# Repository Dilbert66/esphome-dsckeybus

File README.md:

# DSCKeyBus ESPHOME custom component to interface to a DSC POWERSERIES alarm system.

If you like this project and wish to supplement my coffee intake, please click the button below to donate! Thank you!

This is an implementation of an ESPHOME custom component to interface directly to a [DSC POWERSERIES] (https://www.dsc.com/dsc-security-products/g/PowerSeries/4)  alarm system using the keybus interface and  very inexpensive ESP32 modules.  Dsc Classic series is not currently supported.  

*** NOTE *** : The ESP8266 is no longer supported due to it having inadequate resources needed to run the current code base since ESPHome version 2025.7  

Using a heavily modified DSC keybus interface library from https://github.com/taligentx/dscKeybusInterface, it provides full read and write control of the alarm system. The idea and yaml code is based on the DIY example at: https://github.com/Margriko/Paradox-ESPHome.

This library is designed around the "external components" feature of ESPHome (https://esphome.io/components/external_components.html).  The previous version of this library was using the older "custom components" feature which is being deprecated.  Using external components is a much better alternative and allows for much easier install and customization.

To install, first copy the DscAlarm.yaml file from here to your esphome directory. You can then edit it either directly or using the ESPHome dashboard to match your alarm panel setup.  The yaml is self explanatory.  Secondly, for the main library support code installation you have two choices:

 1: You can leave the yaml external_components source line uncommented and it will automatically fetch the required code from my esphome-components repository during the compile.  
 
 or alternatively:
 
 2: If you prefer a more manual approach, you can comment out the github source line and uncomment the source "my_components" line.  You will then need to create a matching my_components directory in your esphome home path.  Name it anything you like as long as it matches the source line in the yaml.  You then copy all content from the "components" directory located in repository https://github.com/Dilbert66/esphome-components/tree/main/ to this new directory. Please note that for any future updates, you will again need to do the copy process.

The following services are published to home assistant for use in various scripts.  Please note that you will also need to have a transistor on the green data line to give you write access to the bus as shown in the wiring diagram.

	alarm_disarm: Disarms the alarm with the user code provided, or the code specified in the configuration.
	alarm_arm_home: Arms the alarm in home mode.
	alarm_arm_away: Arms the alarm in away mode.
	alarm_arm_night: Arms the alarm in night mode (no entry delay).
	alarm_trigger_panic: Trigger a panic alarm.
        alarm_trigger_fire: Trigger a fire alarm.
	alarm_keypress_partition: Sends a string of characters to the alarm system to the selected partition
        set_zone_fault: Triggers a open/close on one of the zone emulator virtual zones
	set_panel_time: Set the time on your panel. For the esp32 on. Automatically syncs the time with an nntp server.
	set_panel_time_manual: Set the time on your panel directly.

These are similar services to those provided by the Envisalink Home Assistant integration (which requires a more expensive Envisalink interface board to be installed in your alarm system panel). See: https://www.home-assistant.io/integrations/envisalink/

A new feature of the firmware is the ability to emulate multiple PC5108 zone adapaters to give you up to 64 zones if your system supports it. Example configuration to add emulation of zones 17-24 in the dscalarm.yaml file.  

Example config: 
```
  #zone expander addresses:
  # 9  - zones 9-16
  # 10 - zones 17-24
  # 11 - zones 25-32
  # 12 - zones 33-40 (for systems with 64 zone support)
  # 13 - zones 41-48 (for systems with 64 zone support)
  # 14 - zones 49-56 (for systems with 64 zone support)
  # 16 - zones 57-64 (for systems with 64 zone support)  
  expanderAddr1: "10" # 1st zone expander emulator address to use . Set to 0 to disable. 
  expanderAddr2: "0" # 2nd expander emulator address to use . Set to 0 to disable. 
```
A new service is also made available in home assistant called  esphome.\<yourdscsystemname\>_set_zone_fault with attributes zone and fault: 
zone is 2 digit zone number and fault is 0 or 1 where 1 sets a zone as open and 0 closes it. By calling this service from a home assistant function, you can enable any event, sensor, etc to trigger any one of your emulated zones in your alarm system.

Relay module support is also added.   This will give your panel the ability to trigger an event on any PGM channel output.  See the yaml file for an example configuration.  An example output for pgm 1 will show in home assistant as <systemname> PGM 1. You can add more fields in the yaml config file.

This version now also adds the ability to display the low battery warning status of any wireless zones.  These will be showng in the "zone status" field of the yaml.   Also in that field, you will see the alarm status, open and bypass statuses of any zones
The display format for a low battery is BL:zz and alarm status will be shown as AL:zz  where zz is the zone number.  Bypass is BY:xx and open is OP:xx.

I've also added a custom alarm panel card with new  functions from the library that provides similar functions as available from an LCD keypad.  This includes the display menus and the ability to fully program your system using full text display of all fields.
	
## Example in Home Assistant

The returned statuses for Home Assistant are: armed_away, armed_home, armed_night, pending, disarmed,triggered and unavailable.  

Sample Home Assistant Template Alarm Control Panel configuration with simple services (defaults to partition 1).

```
alarm_control_panel:
  - platform: template
    panels:
      safe_alarm_panel:
        name: "Alarm Panel"
        value_template: "{{states('sensor.dscalarm_status_partition_1')}}"
        code_arm_required: false
        
        arm_away:
           action: esphome.dscalarm_alarm_arm_away
                  
        arm_home:
           action: esphome.dscalarm_alarm_arm_home
          
        arm_night:
           action: esphome.dscalarm_alarm_arm_night
            data_template:
              code: '{{code}}' #if you didnt set it in the yaml, then send the code here
          
        disarm:
           action: esphome.dscalarm_alarm_disarm
            data_template:
              code: '{{code}}'                    

```

Alternative Home assistant configuration using specified partition with set_alarm_state service.

```
alarm_control_panel:
  - platform: template
    panels:
      safe_alarm_panel:
        name: "Alarm Panel - Partition 2"
        value_template: "{{states('sensor.dscalarm_status_partition_1')}}"
        code_arm_required: false
        
        arm_away:
           action: esphome.dscalarm_set_alarm_state
            data_template:
			  partition: 2
			  state: "A"
			  code: ""
      
        arm_home:
           action: esphome.dscalarm_set_alarm_state
            data_template:
              partition: 2
			  state: "S"
			  code: ""

        arm_night:
           action: esphome.dscalarm_set_alarm_state
            data_template:
              partition: 2
              state: "N"
              code: '{{code}}'  
          
        disarm:
          - service: esphome.dscalarm_set_alarm_state
            data_template:
              partition: 2
              state: "D"
              code: '{{code}}'            
```
## Services

- Basic alarm services. These services default to partition 1:

	- "alarm_disarm", Parameter: "code" (access code)
	- "alarm_arm_home" 
	- "alarm_arm_night", Parameter: "code" (access code)
	- "alarm_arm_away"
	- "alarm_trigger_panic"
	- "alarm_trigger_fire"
    - "set_zone_fault", Parameters: "zone" , "fault" eg zone: 17, fault: 1 (or true) 

- Intermediate command service. Use this service if you need more versatility such as setting alarm states on any partition:

	- "set_alarm_state",  Parameters: "partition","state","code"  where partition is the partition number from 1 to 8, state is one of "D" (disarm), "A" (arm_away), "S" (arm_home), "N" (arm_night), "P" (panic) or "F" (fire) and "code" is your panel access code (can be empty for arming, panic and fire cmds )

- Generic command service. Use this service for more complex control:

	- "alarm_keypress",  Parameter: "keys" where keys can be any sequence of cmds from the list below. For example to arm partition 2  in night mode you set keys to be "/2Nxxxx" where xxxx is your access code. Alternatively you can use the * code for the same function and send /2*9xxxx.   

```
	  case '/': setPartition = true; validKey = false; break;
      case '0':
      case '1': writeKey = 0x05; break;
      case '2': writeKey = 0x0A; break;
      case '3': writeKey = 0x0F; break;
      case '4': writeKey = 0x11; break;
      case '5': writeKey = 0x16; break;
      case '6': writeKey = 0x1B; break;
      case '7': writeKey = 0x1C; break;
      case '8': writeKey = 0x22; break;
      case '9': writeKey = 0x27; break;
      case '*': writeKey = 0x28; writeAsterisk = true; break;
      case '#': writeKey = 0x2D; break;
      case 'F':
      case 'f': writeKey = 0x77; writeAlarm = true; break;                    // Keypad fire alarm
      case 's':
      case 'S': writeKey = 0xAF; writeArm[writePartition - 1] = true; break;  // Arm stay
      case 'w':
      case 'W': writeKey = 0xB1; writeArm[writePartition - 1] = true; break;  // Arm away
      case 'n':
      case 'N': writeKey = 0xB6; writeArm[writePartition - 1] = true; break;  // Arm with no entry delay (night arm)
      case 'A':
      case 'a': writeKey = 0xBB; writeAlarm = true; break;                    // Keypad auxiliary alarm
      case 'c':
      case 'C': writeKey = 0xBB; break;                                       // Door chime
      case 'r':
      case 'R': writeKey = 0xDA; break;                                       // Reset
      case 'P':
      case 'p': writeKey = 0xDD; writeAlarm = true; break;                    // Keypad panic alarm
      case 'x':
      case 'X': writeKey = 0xE1; break;                                       // Exit
      case '[': writeKey = 0xD5; break;                                       // Command output 1
      case ']': writeKey = 0xDA; break;                                       // Command output 2
      case '{': writeKey = 0x70; break;                                       // Command output 3
      case '}': writeKey = 0xEC; break;                                       // Command output 4
```	 

## Custom Alarm Panel Card
I've added a sample lovelace alarm-panel card copied from the repository at https://github.com/GalaxyGateway/HA-Cards. I've customized it to work with this ESP library's services.   I've also added two new text fields that will be used by the card to display the panel prompts the same way a real keypad does. To configure the card, just place the `alarm-keypad-card.js` and `*.mp3` files from the ha_keypad_card folder into the `/config/www` directory of your homeassistant installation and add a new resource in your lovelace configuration pointing to `/local/alarm-keypad-card.js`. <br>
Add a reference to alarm-keypad-card.js in Lovelace. There’s two ways to do that:<br>
1. Using UI:  go to settings (cog icon bottom left in sidebar menu), click on 'dashboards', click on top right 3 dots option then on Resources,
  bottom right 'add resource' option, in window, paste the url as '/local/alarm-keypad-card.js?id=1', select javascript module.

2. Using YAML: Add following code to lovelace section

```yaml
resources:
- url: /local/alarm-keypad-card.js?id=1
  type: module
```
*** NOTE *** :  Every time you update this file, you will need to increase the id=xx number in the url by 1 in order to force the browser to reload it.

### Panel Card example

### Panel card example lovelace configuration

```
type: custom:alarm-keypad-card
title: DSC Keypad
disp_line1: sensor.dscalarm_ln1_1
disp_line2: sensor.dscalarm_ln2_1
service_type: esphome
service: dscalarm_alarm_keypress_partition
status_A: READY
status_B: ARMED
status_C: TROUBLE
status_D: AC
sensor_A: binary_sensor.dscalarm_rdy_1
sensor_B: binary_sensor.dscalarm_arm_1
sensor_C: binary_sensor.dscalarm_tr
sensor_D: binary_sensor.dscalarm_ac
status_A_off_icon: mdi:circle-off-outline
status_A_on_icon: mdi:check-circle
status_A_color: green
status_B_on_icon: mdi:shield-lock
status_B_off_icon: mdi:shield-off-outline
status_B_color: red
status_C_on_icon: mdi:alert
status_C_off_icon: mdi:triangle-outline
status_C_color: orange
status_D_on_icon: mdi:power-plug
status_D_off_icon: mdi:power-plug-off-outline
status_D_color: green

#all style/color settings are optional. These are the default for dark and light modes
style:
  "--lcdbgcolordark": "#859c99"
  "--lcdtextcolordark": "#222"
  "--buttonbgcolordark": var(--input-fill-color)
  "--buttontextcolordark": var(--primary-color)
  "--buttonhovercolordark": var(--outline-hover-color)
  "--buttonactivecolordark": var(--secondary-text-color)
  "--sensorlabelcolordark": var(--accent-color));
  "--buttonfocuscolordark": var(--outline-color)
  "--sensoroffcolordark": var(--disabled-text-color)
  "--bordercolordark": var(--disabled-color)

  "--sensoroffcolorlight": var(--disabled-text-color)
  "--lcdbgcolorlight": "#859c99"
  "--lcdtextcolorlight": "#222"
  "--sensorlabelcolorlight": var(--accent-color));
  "--buttonbgcolorlight": var(--input-fill-color)
  "--buttontextcolorlight": var(--primary-color)
  "--buttonhovercolorlight": var(--outline-hover-color)
  "--buttonactivecolorlight": var(--secondary-text-color)
  "--buttonfocuscolorlight": var(--outline-color)
  "--bordercolorlight": var(--disabled-color)

button_A: STAY
button_B: AWAY
button_C: NIGHT
button_D: CHIME
button_E: ""
button_F: <
button_G: ">"
button_H: ""
cmd_A:
  keys: S
  partition: 1
cmd_B:
  keys: W
  partition: 1
cmd_C:
  keys: "N"
  partition: 1
cmd_D:
  keys: C
  partition: 1
cmd_F:
  keys: <
  partition: 1
cmd_G:
  keys: ">"
  partition: 1
key_0:
  keys: "0"
  partition: 1
key_1:
  keys: "1"
  partition: 1
key_2:
  keys: "2"
  partition: 1
key_3:
  keys: "3"
  partition: 1
key_4:
  keys: "4"
  partition: 1
key_5:
  keys: "5"
  partition: 1
key_6:
  keys: "6"
  partition: 1
key_7:
  keys: "7"
  partition: 1
key_8:
  keys: "8"
  partition: 1
key_9:
  keys: "9"
  partition: 1
key_star:
  keys: "*"
  partition: 1
key_pound:
  keys: "#"
  partition: 1
text_1: BYPASS
text_2: SERV
text_3: ALARMS
text_4: CHIME
text_5: CODES
text_6: FUNC
text_7: OUTP
text_8: PROG
text_9: NIGHT
text_star: SELECT
text_pound: ENTER
text_0: ""
beep: binary_sensor.dscalarm_bp_1
button_disabled_A: false
button_disabled_B: false
button_disabled_C: false
button_disabled_D: false
button_disabled_E: true
button_disabled_F: false
button_disabled_G: false
button_disabled_H: true
scale: 1
left_buttons: false
view_bottom: true

```	

## MQTT Support
If you would like to use MQTT communications with Homeassistant or alternatively use ESPHOME with other platforms that can support MQTT, you can modify the configuration to use the MQTT protocol instead of the native HA API integration.  This simply involves the addtion of an mqtt: configuration section in the yaml and to remove the api: section.   Please see the ESPHOME MQTT documentation more details: https://esphome.io/components/mqtt.html .  For an example on how to configure the alarm-panel-card to use MQTT services, please see the lovelace.yaml file.  

Command topic is "&lt;yoursystemnameinesphome&gt;/alarm/set"
	
Command payload for sending key commands: {"keys":"&lt;sequenceofkeys&gt;","partition":&lt;partition#&gt;}
	
Command payload to set an expander fault status: {"zone":&lt;zone#&gt;,"fault":&lt;on:off or 0:1&gt;}
	
Command payload to set an alarm state: {"state":"&lt;alarmstate&gt;","partition":&lt;partition#&gt;,"code":"&lt;accesscode&gt;"} - see set_alarm_state api command above for more details

Sensor data will follow the HA MQTT discovery format. See here for details: https://www.home-assistant.io/docs/mqtt/discovery/

If you prefer to use Arduino instead of ESPHome, I've also provided an Arduino example sketch in the mqtt_example folder.  Follow the instructions at the top of the file.
	
## Wiring
### Mosfet level converter version - recommended

Notes: You need to set dscreadpin = dscwritepin in the yaml config.  eg: dscwritepin: 21, dscreadpin: 21, dscclockpin: 22
This version uses a bidrectional read/write configuration for the green line. The yellow line is read only.
Thanks to utmba95 for the design suggestion and testing.

### Resistor divider version	

Notes: Write access to the Keybus requires an NPN transistor and a resistor.  Most small signal NPN transistors should be suitable.

## Optocoupler ground isolated version

* esp32: connect the DSC lines to GPIO pins that are normally low to avoid putting spurious data on the Keybus: GPIO22, GPIO21 and GPIO18.

* When powering the ESP from an external power supply such as USB (recommended) ensure you still connect the ground to the DSC panel if you are not using the isolated circuit version.

## Useful tools
jpmeijers has generously provided a python script to allow getting the installer code from a DSC panel.  See the README and associated files in the extras\crack_installer_code folder

## References
* ESPHOME yaml and component structure based on code from https://github.com/Margriko/Paradox-ESPHome
* Wiring and DSC library from https://github.com/taligentx/dscKeybusInterface
* ESPHOME diy examples from https://esphome.io/guides/diy.html
* Thanks to jpmeijers for the unlock script
* Also many thanks to the various people who have helped updating this library by testing and posting logs.

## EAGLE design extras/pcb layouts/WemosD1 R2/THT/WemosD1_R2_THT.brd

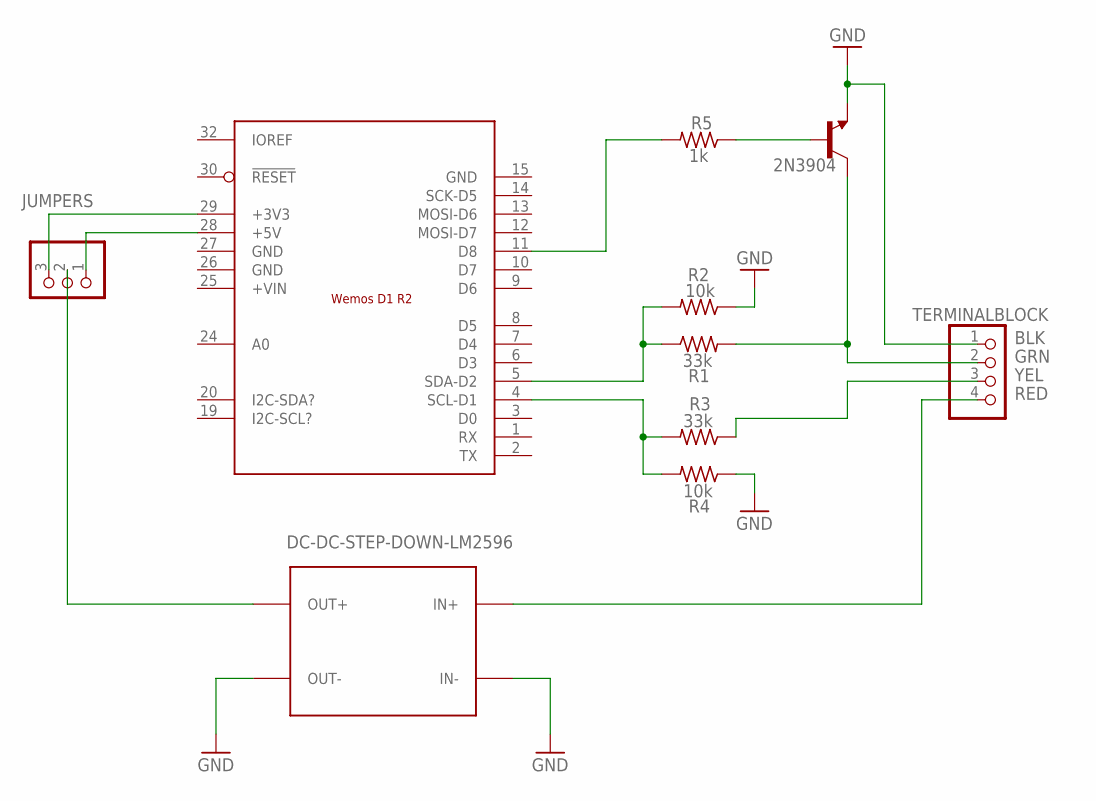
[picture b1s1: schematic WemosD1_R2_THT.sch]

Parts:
JUMPERS: PINHD-1X3; 1X03
R1, R3: 33k; 0204/7
R2, R4: 10k; 0204/7
R5: 1k; 0204/7
T1: 2N3904; TO92
TERMINALBLOCK: PINHD-1X4; 1X04
U$1: WEMOS_D1_R2
U$2: DC-DC-STEP-DOWN-LM2596

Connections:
GND: R2.1, R4.1, T1.3 (E), TERMINALBLOCK.1, U$1.15 (GND), U$1.26 (GND), U$1.27 (GND), U$2.IN-, U$2.OUT-
unnamed: R1.1, R2.2, U$1.5 (SDA-D2)
unnamed: JUMPERS.2, U$2.OUT+
unnamed: R3.2, R4.2, U$1.4 (SCL-D1)
unnamed: R3.1, TERMINALBLOCK.3
unnamed: TERMINALBLOCK.4, U$2.IN+
unnamed: R5.1, T1.2 (B)
unnamed: R5.2, U$1.11 (D8)
unnamed: JUMPERS.3, U$1.29 (+3V3)
unnamed: JUMPERS.1, U$1.28 (+5V)
unnamed: R1.2, T1.1 (C), TERMINALBLOCK.2

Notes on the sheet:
RED
YEL
GRN
BLK

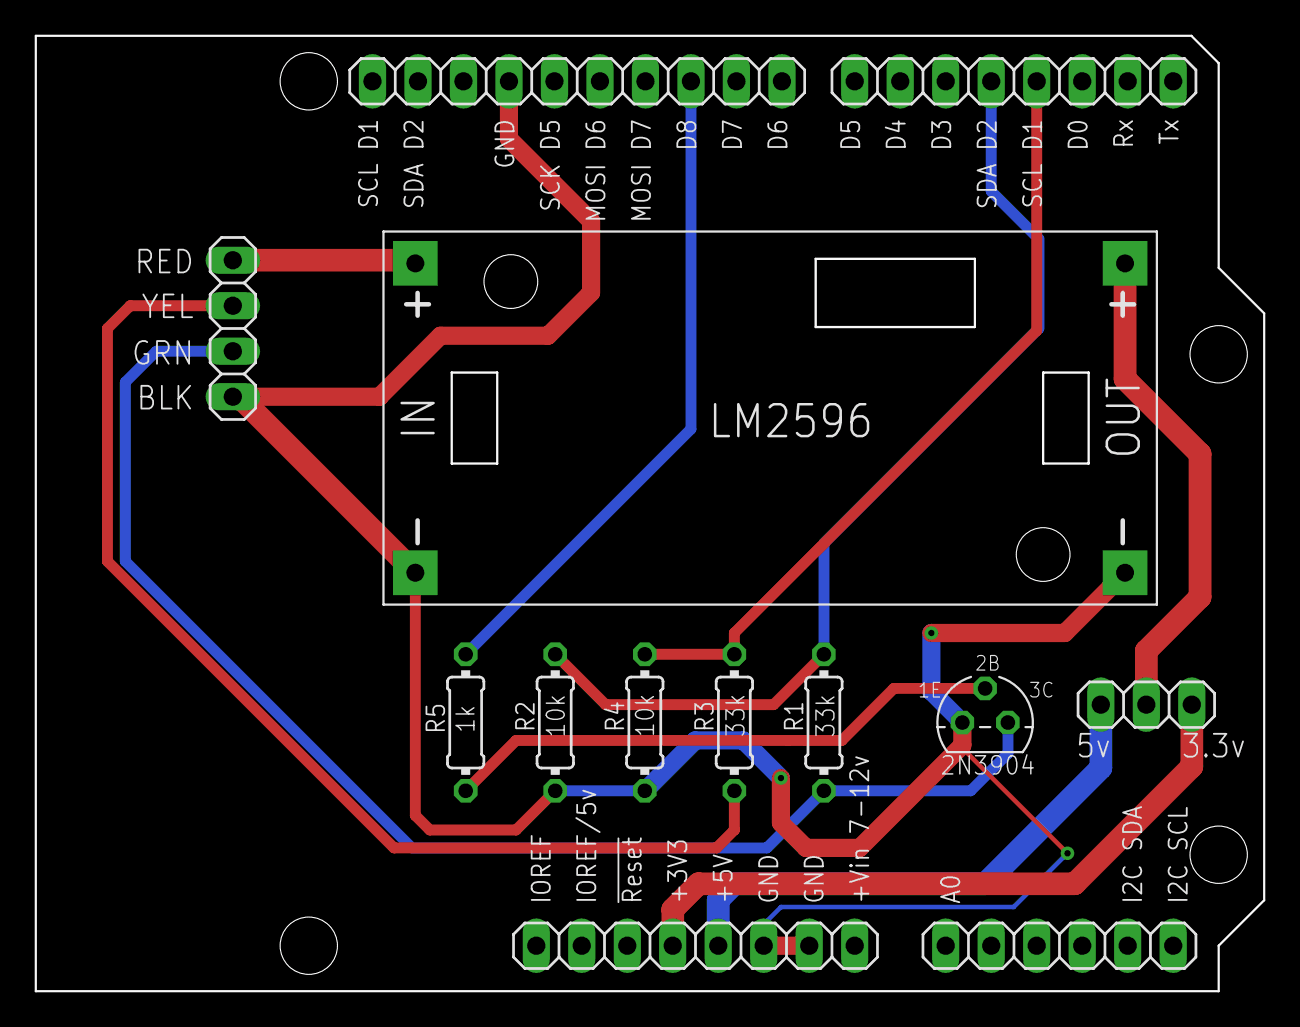
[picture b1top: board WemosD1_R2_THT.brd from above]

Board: 2 copper layers, 68.6 x 53.3 mm, 10 parts (0 on the bottom side), 11 nets.

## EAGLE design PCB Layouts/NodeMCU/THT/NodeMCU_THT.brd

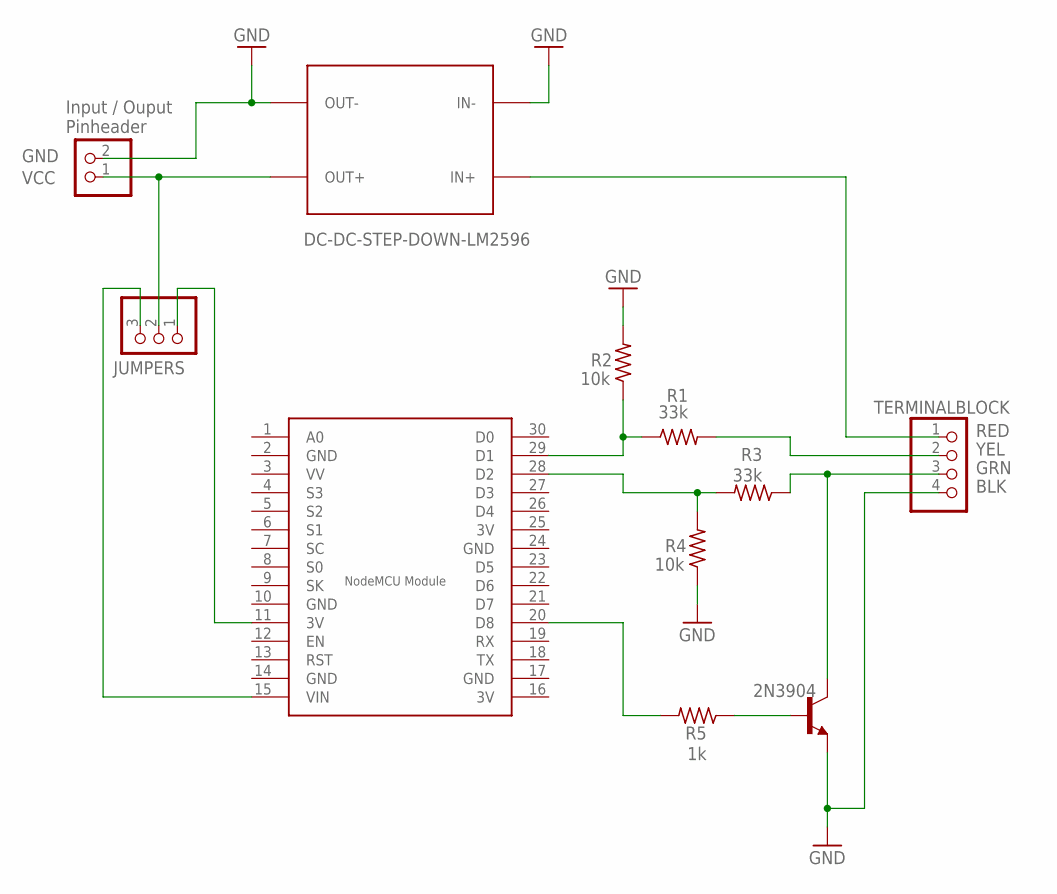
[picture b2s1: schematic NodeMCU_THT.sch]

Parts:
JP2: PINHD-1X2; 1X02
JUMPERS: PINHD-1X3; 1X03
R1, R3: 33k; 0204/7
R2, R4: 10k; 0204/7
R5: 1k; 0204/7
T1: 2N3904; TO92
TERMINALBLOCK: PINHD-1X4; 1X04
U$1: NODEMCU
U$2: DC-DC-STEP-DOWN-LM2596

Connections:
3V: U$1.16 (3V), U$1.25 (3V)
GND: JP2.2, R2.2, R4.1, T1.3 (E), TERMINALBLOCK.4, U$1.2 (GND), U$1.10 (GND), U$1.14 (GND), U$1.17 (GND), U$1.24 (GND), U$2.IN-, U$2.OUT-
unnamed: R1.1, R2.1, U$1.29 (D1)
unnamed: R1.2, TERMINALBLOCK.2
unnamed: R3.2, R4.2, U$1.28 (D2)
unnamed: R3.1, T1.1 (C), TERMINALBLOCK.3
unnamed: TERMINALBLOCK.1, U$2.IN+
unnamed: JP2.1, JUMPERS.2, U$2.OUT+
unnamed: R5.1, T1.2 (B)
unnamed: R5.2, U$1.20 (D8)
unnamed: JUMPERS.3, U$1.15 (VIN)
unnamed: JUMPERS.1, U$1.11 (3V)

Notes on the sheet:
NodeMCU Module
RED
YEL
GRN
BLK
GND
VCC
Input / Ouput Pinheader

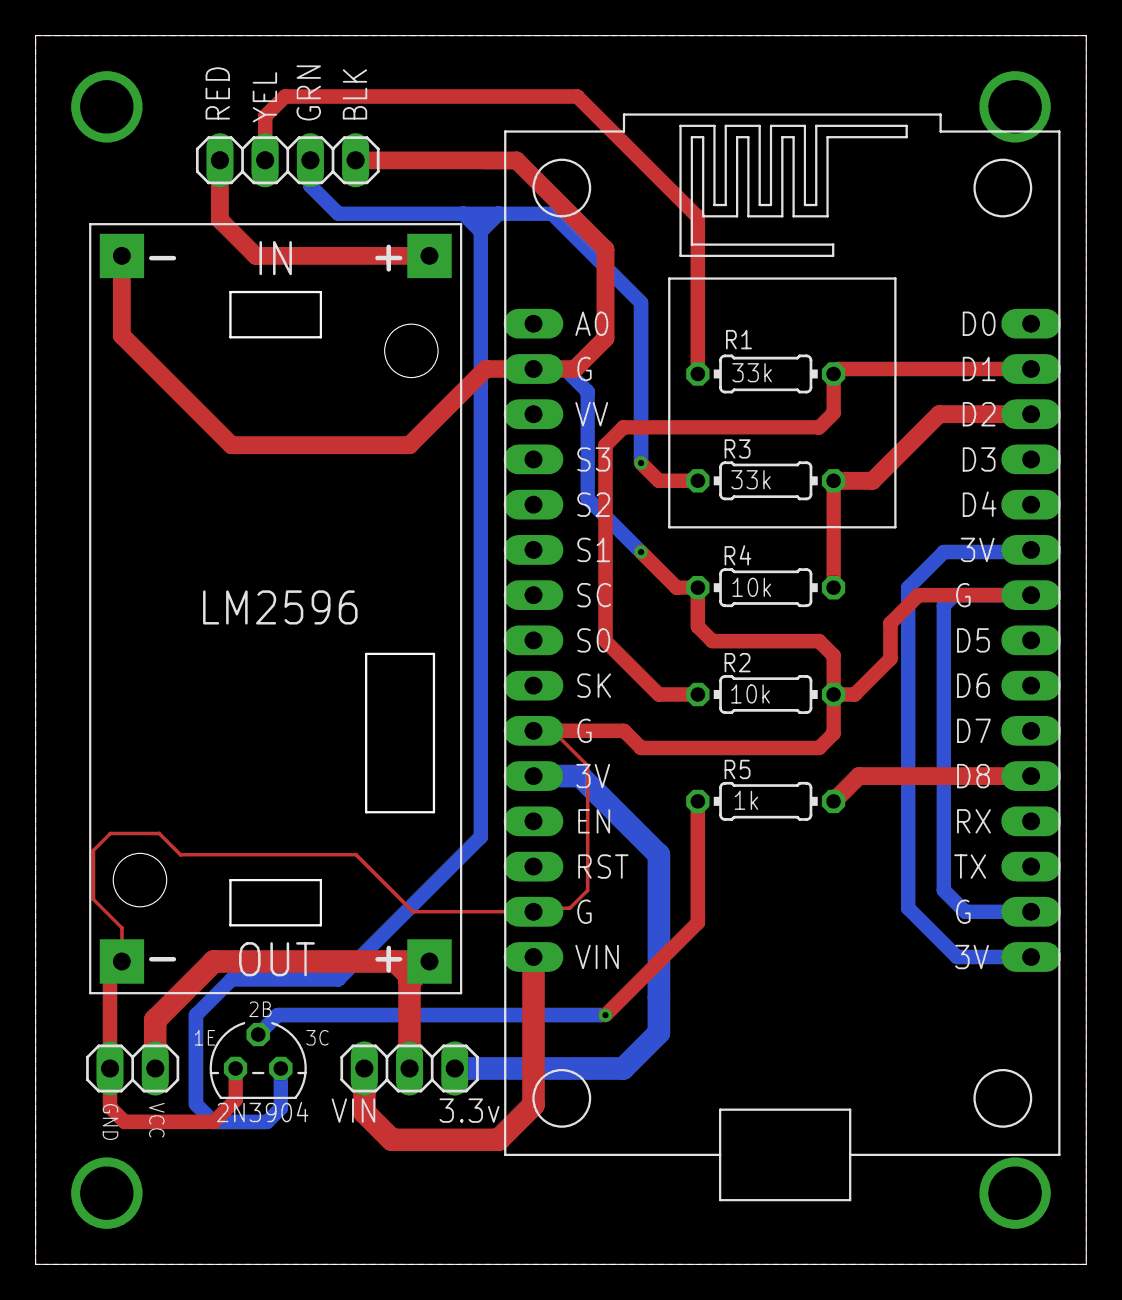
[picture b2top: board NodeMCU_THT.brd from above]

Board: 2 copper layers, 59.0 x 69.0 mm, 11 parts (0 on the bottom side), 12 nets.

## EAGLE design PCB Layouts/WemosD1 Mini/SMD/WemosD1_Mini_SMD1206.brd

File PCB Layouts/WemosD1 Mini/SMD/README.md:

DSC Alarm Shield for WemosD1 Mini and WemosD1 Mini PRO
==================================

Getting started
------------
Tools you will need:

 * Multimeter or Digital Voltimeter
 * Soldering Iron and thin tip
 * Soldering Wire, best quality you can get, 0.5mm recomended or lower for SMD components, 0.8mm for the rest of components
 * Isopropilic Alcohol (to clean your board once finished)
 * Small (-) screwdriver
 * (Optional) Flux and Soldering Paste

Materials and Components:
 * 8 Female Headerpins x2
 * 3 Male Headerpins
 * 1 Two Pin jumper
 * 1206 SMD resistor 33k x2
 * 1206 SMD resistor 10k x2
 * 1206 SMD resistor 1k
 * 2N3904 or 2N2222 Transistor
 * LM2596 Module
 * 4 Terminal Blocks (can be 2 terminal blocks x2)
 * Optional: M3 screws or standoffs / spacers to secure the board. x4

How to order
------------
If you think that the board is enough and you dont need to modify it, you can download the `gerber.zip` file and that's all. PCB manufacturer will ask for that file in order for you to start building the board.
There are a lot of chinese webpages where you can order 5 units for about 2-10 dollars, just choose one where the shipping cost isn't too high in your country.

Some popular sites:

[All PCB](https://www.allpcb.com/?Mb_InviteId=69183) (For Chile Recomended via EMS)

[JLCPCB](https://jlcpcb.com/)

[PCBway](https://www.pcbway.com/setinvite.aspx?inviteid=432106)

You can order the rest of the components on Aliexpress (my favorite) or you may buy them locally at any electronic store.

Building
------------

**Considerations:** Work on a clean area and clean your board first before you start soldering.

1. Solder all resistances first. Make sure to place the correct values on the labeled pads.

2. Solder the transistor.

3. solder the terminal blocks.

4. solder the headerpins.

5. Last, solder the LM2596 Module.

6. After finish clean your board.

Installing to your DSC Alarm Panel
------------

:warning: **IMPORTANT:** Please follow these instructions. Plug the jumper in the wrong place without adjusting the LM2596 voltage first, may fry your ESP8266.
Before installing make sure all removable components are disconected. WemosD1 Mini and jumper MUST BE DISCONECTED.

Optional: Before installing it’s recommended that you secure the board using an enclosure, standoffs/spacers or screw it on a non conductive surface. A quick way is to just cover the bottom of the circuit with electrical tape.

1. Plug the board to the DSC Alarm Panel.

:warning: **Warning** I recommend unplugging your DSC alarm panel from power first, including the battery, before you plug the board in. This is to avoid any short circuit mistake when manipulating powered cables.

Connect each terminal labeled, RED-RED, YEL-YEL, GRN-GRN, BLK-BKL. Then you may power your DSC Alarm Panel again. If everything is ok, a blue LED should light on the LM2596 module.

2. Regulate the LM2596 module to the right voltage:
With a multimeter, place the points on the OUT + and - pads and measure the voltage.

Use a small (-) screwdriver and turn the patentiometer to start to drop the voltage till 3.3v (highly recommended)
**Double check the voltage and ensure you set the correct tension**

3. Plug your WemosD1 Mini / WemosD1 Mini PRO facing as the board footprint. Make sure that pins labeled on the board match. **Don't forget load the firmware first**

4. Place the jumper at the selected voltage.

:warning: **Warning: Regulating the LM2596 with 5v or more and plugging the jumper on 3.3v pin may fry your ESP8266. Be sure to plug the jumper in the correct position.**

And you're ready to go!

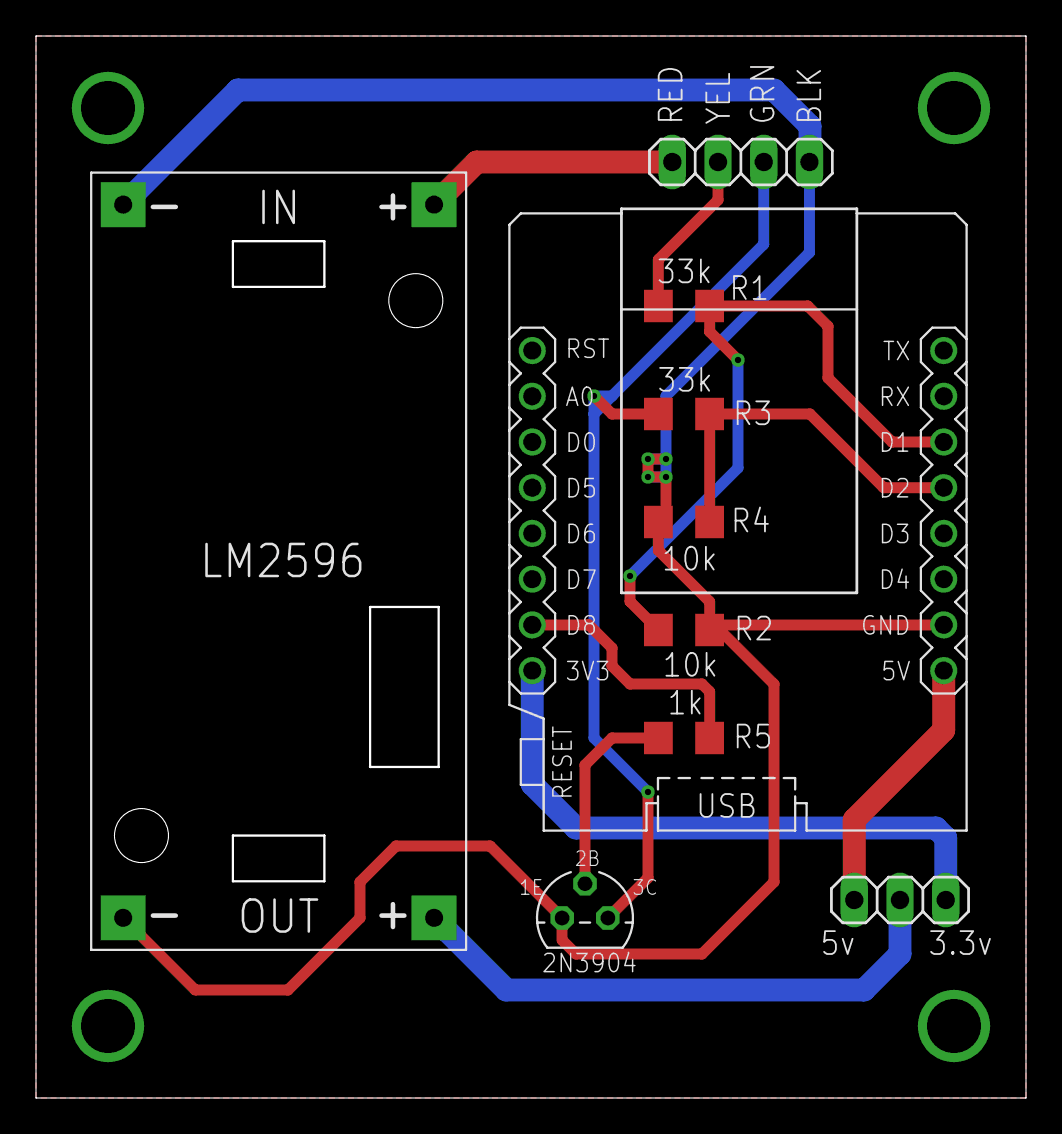
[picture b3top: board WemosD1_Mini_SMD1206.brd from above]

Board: 2 copper layers, 55.0 x 59.0 mm, 10 parts (0 on the bottom side), 11 nets.

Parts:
JUMPERS: 1X03
R1, R3: 33k; R1206
R2, R4: 10k; R1206
R5: 1k; R1206
T1: 2N3904; TO92
TERMINALBLOCK: 1X04
U$1: WEMOS-D1-MINI
U$2: DC-DC-STEP-DOWN-LM2596

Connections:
GND: R2.2, R4.1, T1.3, TERMINALBLOCK.4, U$1.JP2.7, U$2.IN-, U$2.OUT-
unnamed: R1.1, R2.1, U$1.JP2.3
unnamed: R1.2, TERMINALBLOCK.2
unnamed: R3.1, R4.2, U$1.JP2.4
unnamed: R3.2, T1.1, TERMINALBLOCK.3
unnamed: TERMINALBLOCK.1, U$2.IN+
unnamed: JUMPERS.2, U$2.OUT+
unnamed: R5.1, T1.2
unnamed: R5.2, U$1.JP1.7
unnamed: JUMPERS.3, U$1.JP2.8
unnamed: JUMPERS.1, U$1.JP1.8

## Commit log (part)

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2022-05-07 - event info partition display logic correction
2022-05-07 - shortned event messages for display on one line
2022-05-07 - fixed issue with beeps not working - fixed issue with multi field entries
2022-05-07 - shorten event msg to fit
2022-05-07 - only write to unlocked partition
2022-05-07 - show system unavailable when locked and key pressed
2022-05-07 - removed uneccesary for loop
2022-05-08 - menu navigation fixes
2022-05-09 - menu logic reconfiguration - added output control menu
2022-05-09 - increased write buffer to 20 to allow longer cmds sequences - fix issue with user control write - removed debug comments
2022-05-09 - formatting , indenting cleanup - removed uneeded debug comments
2022-05-09 - fixed introduced double digit issue
2022-05-09 - fixed issue with options not refreshing in programming
2022-05-09 - fixed another missed extra sent key
2022-05-09 - enabled extended zone status text field as well as trouble field
2022-05-10 - various menu handling fixes
2022-05-11 - added real time clock to log display - added ability to set chip pins from yaml config - added event logging - various other fixes
2022-05-12 - fixed missing module logging
2022-05-12 - added commented encryption key setup
2022-05-12 - added preliminary time set function via it-100 command
2022-05-12 - added partition check in 05 - added version check - other small fixes
2022-05-13 - added maxzones config parameter to yaml - corrected issue with duplicate event empty messages
2022-05-13 - fix issue with autosubmit in time entry
2022-05-13 - corrected encryption line location in yaml
2022-05-13 - converted menu options to be more multi partition friendly
2022-05-13 - menu tweaks when handling user codes
2022-05-17 - moved menu strings to flash storage to reduced ram useage - added delayed cmd stand to retrieve battery levels - optimized main loop for sensor updates - other fixes
2022-05-17 - removed unecessary check in write routine
2022-05-17 - increased keypress waittime
2022-05-18 - reduced IRAM useage by using a buffer pointer and precalculating chksums
2022-05-18 - added periodic refresh every minute - fixed incorrect output control menu - removed uneccessary menu lines
2022-05-18 - corrected issue with zones not refreshing correctly
2022-05-18 - removed duplicate message during refresh
2022-05-19 - fixed issue with older panels not showing events
2022-05-20 - fixed issue with zones 9-16 not being recognized
2022-05-20 - fixed issue with enabled zones not correctly set
2022-05-20 - break out of loop instead of return
2022-05-20 - delayed zoneclear on boot
2022-05-20 - added access code to name mapping in the yaml for event messages
2022-05-20 - fixed global syntax
2022-05-20 - fixed issue with user codes not showing active over 32
2022-05-21 - corrected keypress service in lovelace yaml
2022-05-21 Update README.md
    Updated documentation
2022-05-22 - removed uneeded web-server: section as it's unsecure, uneeded and increases ram useage
2022-05-23 - add macro for constructor to allow calling custom component functions within lambda - change set_panel_time() to public function - add id to lambda
2022-05-24 - modified all static strings to use progmem - fixed editidx warning - ram useage optimizations
2022-05-25 - more memory optimizations - removed uneeded debug comments and functions
2022-05-26 - switched esp8266 to component instead of polling component - a few more memory optimizations - defaulted cmd05/1b filter
2022-05-27 - removed uneeded comment in yaml
2022-06-01 - corrected issue with some system messages overriding status on refresh
2022-06-01 - added initial trouble msg status clear
2022-06-01 - added check before updating panel status
2022-06-02 - automatically fetch trouble statuses on trouble light change
2022-06-02 - force clear of trouble msg on trouble reset
2022-06-07 - removed uneeded yaml comment
2022-06-07 - added additional comments to mqtt section
2022-06-07 Update README.md
    Added mqtt service descriptions to readme
2022-06-10 - mqtt fixes for esp32 version
2022-09-23 - corrected compile for mqtt and realtime clock
2022-09-25 - added conditional compile options for debug
2022-09-26 - small write function change to test issue
2022-10-06 - added test version of dscalarm.h to test issue with wifi connectivity
2022-10-08 - test using timer1 instead of timer0 on ESP to see if it helps wifi connectivity for some users - removed test defines
2022-10-25 Add files via upload
    Add WT32-ETH01 with thru-hole or SMD resisters
2022-10-25 Create WT32-ETH01
2022-12-15 - fix issue with new esphome and timer processing
2022-12-30 - correct issue with incorrect chksum calculated for expander
2023-01-09 - clean up comments - fix compile issue with arduino
2023-01-11 - added arduino mqtt example
2023-01-12 - fix incorrect pin number for dscclockpin in mqtt example
2023-01-12 - removed merge conflicts
2023-01-12 - update readme
2023-01-16 - added standalone virtual keypad example with added telegram push functionality
2023-01-17 - removed some warnings during compilation
2023-01-17 - clarified some details
2023-01-18 - added helper tips to sketch
2023-01-18 - added bit field statuses to partition states for easier access - added more statuses for display to sketch
2023-01-18 - increase string buffer size
2023-01-19 - clean up formatting
2023-01-19 - corrected issue with missing prefix message header - added /setpassword cmd to bot to allow changin keypad password - increased telegram task memory - defaulted notificationFlag to 255 in order to 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
2023-01-20 - small bugfix
2023-01-21 - remove errant print
2023-01-21 - fix issue with panel time not setting correctly - increased task stack space
2023-01-21 - added test for valid time before setting panel time
2023-01-21 - added missed define exclusion
2023-01-22 - fixed compilation errors when not using virtualkeypad
2023-01-22 - added elegant ota support
2023-01-23 - documentation updates - added message on initial start - removed uneeded code
2023-01-24 - code cleanup
2023-01-24 - fix chime status initialization
2023-01-28 - control refresh correctly for partition change
2023-02-02 - switch from strcat to string on dsc mqtt example - remove some debug messages from index.html
2023-02-07 - corrected battery status update
2023-02-20 - fixed missing or
2023-02-25 - remove unecessary debug message
2023-03-05 - renamed source directory to src for use in platformio - added library.properties file
2023-03-06 - added auto arm programming to menu
2023-03-06 - fix issue with options not updating correctly iin programming mode
2023-03-06 - revert last change.
2023-03-07 - clear upper programzones range on first access
2023-03-29 - update deprecated icache_ram_attr
2023-04-06 - converted custom keypad card from polymer to lit elements - added configurable button row to display on right or left of keypad
2023-05-20 renamed src dir back to dsckeybusinterface
2023-07-19 - fix issue with timeralarmdisable being called with null timer instance
2023-07-19 - only disable timer if not null
2023-07-23 - fix incorrect timer name use
2023-08-03 - changed all debug prints to info
2023-10-20 - remove avr and replace icache_iram with iram_attr
2023-10-20 - corrected alarm zones statuses
2023-10-21 - added partition alarm binary sensors to yaml - fixed issue with zone alarms not being saved correctly - reset sensors to default values on boot in yaml
2023-10-21 - more yaml changes
2023-10-21 - fixed missing ifdef
2023-10-22 - removed uneeded test code from yaml - some wording changes
2023-10-25 - fixed zone alarm clearing
2023-10-29 - removed debug command in example simpliefied yaml
2023-10-30 - reset msg fields to sane value on startup - leave last event msg active instead of clearing after timeout
2023-11-08 - added components code. Reorganize
2023-11-08 - config file fixes
2023-11-09 - deleted old lib code
2023-11-09 - changed to dev components linke
2023-11-09 - removed merge artifacts
2023-11-13 - mqtt section tweaks
2023-12-05 - update doc to clarify manual install
2023-12-21 - remove namspace from disconnect command
2024-03-21 Add python script to crack installer code.
2024-04-15 - fix zone6 entry in yaml
2024-05-07 - point source link to dev branch
2024-05-30 - update yaml example to use template_alarm component
2024-06-02 - reorganize directory
2024-06-02 - point to dev components directory
2024-06-02 - added extra # to cmd
2024-06-03 - added installer code retriever version that uses the web api
2024-06-03 - use type id for field
2024-06-03 - simplify code a bit
2024-06-03 - updated field naming
2024-06-04 - refactor end_run location
2024-06-04 - send ## at end of run to exit installer mode
2024-06-11 - re-add wait for zone open/ready status in dsc scripts
2024-06-11 - speed up installer code scripts
2024-06-11 - readme updates
2024-06-12 - added install code cracker that uses the esphome api. - updated readme
2024-06-12 - added missing virtual environment statments in readme for a linux install
2024-06-12 - tweak scripts with control-c handling
2024-06-29 - updated dscalarm.yaml with template_alarm platform config - added api crack example
2024-08-04 - changed entry_delay to pending and exit_delay to arming
2024-08-04 - set default to false for detailed_partition_state
2024-08-04 Update DscAlarm.yaml - BH updates
2024-08-30 - remove alarm_panel suffix from dscalarm.yaml
2024-10-24 - updated yaml and readme for new config
2024-10-31 - fixed ota section, commented out on_begin due to esphome bug
2024-11-08 - added timed loop variables in dsc yaml
2024-11-08 - revert default to trouble check
2024-11-27 - enlarge display window to allow for larger event messages
2024-12-06 - updated yaml config to new code
2024-12-20 - removed uneeded option
2025-01-11 - added haptic feed back on buttons
2025-01-12 - decrease default vibration duration
2025-01-12 - increase opacity on touch
2025-03-15 Enhanced alarm keypad card js module
    Maintain full width on mobile devices, modern colors, color states on status icons, disabled keys support, updated readme
2025-03-15 Keypad - fix dark mode
2025-03-20 - added icon configuration to keypad card - added support for dark/lite mode on display
2025-03-20 - fix status e
2025-03-21 - use color as parameter in keypad
2025-03-21 -update readme
2025-03-21 - update lovelace.yaml with correct example
2025-03-21 - revert design back to simplified buttons. - add border around lcd
2025-03-24 - updated lit version to 4.x.x using unpkg link - added ability to customize card colors from config
2025-03-25 - some cosmetic tweaks
2025-03-26 - more cosmetic tweaks
2025-03-30 - add ability to control card colors using style option
2025-03-30 - removed uneeded value
2025-03-31 - added ability to control styling and colors
2025-05-21 - add note to readme
2025-07-16 - added custom_services to api section
2025-07-17 - revert back
2025-07-17 - update yaml to new version config
2025-08-10 - updated readme
2025-08-18 - updated yaml sample
2025-08-19 - added extras directory
2025-08-20 - updated crack scripts to latest code messages
2025-10-30 - added undefined state check for line display - corrected default sensor names
2025-10-30 - corrected sensor names to match example yaml
2025-10-30 - updated missed sensor names
2025-10-30 - updated missed sensors
2025-11-07 - change friendly name to match name
2025-11-07 - changed friendly name to match name
2025-11-14 - add beep display
2025-12-06 - [keypadcard] added dsc version with custom icons - [keypadcard] added stub config to keypad card
2025-12-06 [webkeypad] added dsc specific card, added stub config [webkeypad] fixed update issue with 2025.11 ha update
2025-12-08 - fix trigger msg on dsc card
2025-12-08 - fix trigger msg on card
2026-03-14 - [card] add confirmation option to cmds

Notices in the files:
parts and their libraries:
diy-modules: Released under the Creative Commons Attribution 4.0 International License: http://creativecommons.org/licenses/by/4.0
